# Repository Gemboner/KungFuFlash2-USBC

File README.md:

# Kung Fu Flash 2 USB-C

Cartridge for the Commodore 64 that packs a punch.

This repository is a fork of [KungFuFlash2-USBC](https://github.com/Sgw32/KungFuFlash2-USBC) which is a fork of an earlier version of [KungFuFlash2](https://codeberg.org/KimJorgensen/KungFuFlash2) from Kim Jørgensen that was later moved to Codeberg and is still being updated.

To have the "best of both worlds" (USB-C and updated firmware) this repository merged both of them together and additionally introduces some small fixes to the PCB and the production files.

Kung Fu Flash 2 is the big brother of [Kung Fu Flash](https://codeberg.org/KimJorgensen/KungFuFlash). It has a faster microcontroller with more memory and I/O pins, allowing for additional functionality.

**Currently, this project is considered experimental** and provides the same features as Kung Fu Flash, with these notable exceptions:

* CRT files are loaded into RAM, not flash, making large CRT files startup faster. However, changes to EasyFlash cartridges are lost if power is turned off, unless saved via the menu first
* The cartridge detects if the C64/C128 is reset. This allows the use of an additional reset button on the C64 or the built-in reset button on the C128
* REU emulation has been added

Kung Fu Flash 2 can emulate different cartridge types, load PRG files and use D64 disk images.
Just place your desired CRT, PRG or D64 files on a FAT formatted microSD card and use the built-in launcher to execute them.

## Hardware (Rev. 2)

There are three buttons on the cartridge; a reset button, a menu button for starting the launcher, and a special button that is used by the freezer cartridges.

A very nice case has been designed by [Bigby](https://www.printables.com/@Bigby) and can be found on [Printables](https://www.printables.com/model/119330-kung-fu-flash-cartridge-case).

Changes in hardware revision 2 are a USB-C port (including resistors) instead of micro-USB and a different crystal.

As all credits still go to Kim Jørgensen for this great cartridge, the PCB still shows his Codeberg URL.

The gerber files and BOM can be found [here](./hardware/gerber/).

## Supported Cartridges

The following cartridge types are currently supported:

* Generic cartridge (8k, 16k, Ultimax)
* Action Replay v4.x/v5/v6
* KCS Power Cartridge
* Final Cartridge III(+)
* Simons' BASIC
* Fun Play, Power Play
* Super Games
* Ocean type 1
* Epyx Fastload
* C64 Game System, System 3
* WarpSpeed
* Dinamic
* Zaxxon, Super Zaxxon
* Magic Desk, Domark, HES Australia
* Super Snapshot v5
* Comal-80
* Ross
* EasyFlash
* Prophet64
* Freeze Frame
* Freeze Machine
* MACH 5
* Pagefox
* RGCD, Hucky
* Drean
* C128 Generic cartridge (external function ROM)
* WarpSpeed 128

## Supported File Types

The following file types are currently supported:

* Cartridge (CRT)
* C64/C128 generic cartridge (ROM, BIN)
* Disk image (D64, D71, D81)
* Tape image (T64)
* Program (PRG, P00)
* SID tune (SID)
* Firmware update (UPD)
* Text document (TXT, NFO, 1ST)

## SID Playback

SID tunes can be played directly from the launcher. This feature is inherited from the
[KungFuFlash2-USBC](https://github.com/Sgw32/KungFuFlash2-USBC) fork and is not part of the original Kung Fu Flash 2.

Selecting a SID file in the file options menu offers two actions:

* "Play" (RETURN) converts the tune and starts it immediately
* "Convert to PRG" (SHIFT+RETURN) writes a PRG file next to the SID file and returns to the launcher

In both cases the tune is converted to a PRG containing a small BASIC starter and a raster interrupt player,
so the resulting file can also be used on any other C64 setup. As the PRG is written to the microSD card,
the card must not be write protected.

PSID and RSID files of version 1 to 3 are supported, with these limitations:

* Only the first subtune is played; the tune and subtune information from the SID header is ignored
* The player uses a single speed raster interrupt, so multi speed tunes will play at the wrong tempo
* Tunes that load below $0843 cannot be converted, as this area is occupied by the BASIC starter and the player

## REU Emulation

Kung Fu Flash 2 can emulate a 1 Mb REU (RAM Expansion Unit) simultaneously with disk drive emulation.
The REU is enabled in the settings menu (F5) and active when:

* A program is executed using the default option (RETURN)
* A disk image or directory is mounted using "Mount" in the file options menu (SHIFT+RETURN)
* BASIC is started via F6 (C128) or F7 (C64) in the launcher

The REU will not be active when emulating cartridges (CRT files)

## USB Port

The USB port allows programs or disk images to be transferred from/to a PC using the EasyFlash 3 USB protocol.
The USB port is active when:

* The Kung Fu Flash 2 launcher is running
* A program is started using "Load" in the file options menu (SHIFT+RETURN)
* BASIC is started via F7 in the launcher **and** REU emulation is disabled in the settings menu (F5)

Kung Fu Flash 2 shows up as a standard serial port when connected to a PC not requiring any custom drivers to be installed.
This means, however, that the EasyFlash 3 program on the PC side must be modified to support Kung Fu Flash.

The repository of the original Kung Fu Flash contains a modified version of [EasyFlash 3 USB Utilities](https://codeberg.org/KimJorgensen/KungFuFlash/src/branch/master/3rd_party/ef3utils)
and [EasyFlash 3 BBS](https://codeberg.org/KimJorgensen/KungFuFlash/src/branch/master/3rd_party/ef3bbs) which will also work with the Kung Fu Flash 2.

## Firmware Update

Just place the KungFuFlash2_v2.xx.upd file on the SD card and select the file in the launcher to initiate the firmware update.
The newest firmware can be found [here](https://github.com/JuergenLeber/KungFuFlash2-USBC/releases).

For initial firmware installation, [see here](firmware/README.md).

## Limitations

Kung Fu Flash 2 is a so called Software Defined Cartridge where a fast microcontroller emulates cartridge hardware in software.
This makes it extremely flexible, allowing different cartridge types to be supported at a relative low cost.

However, it can be challenging to get the C64 bus timing correct in software and in some places the timing is very close to the limit.
Even though Kung Fu Flash 2 has been tested on different models of the Commodore 64, there is a chance that it doesn't work correctly on your specific model, or requires [phi2 offset adjustment](firmware/README.md#diagnostic).
Use it at your own risk!

Kung Fu Flash 2 will work with the PAL and NTSC version of the Commodore 64 or Commodore 128.

Disk drive emulation is using kernal vectors and will not work with fast loaders or software that uses direct hardware access which a lot of games does.
Currently REL files are not supported and only a subset of the Commodore DOS commands are supported.

## Thanks

Kung Fu Flash 2 was based on or uses other open source projects:

* [Kung Fu Flash](https://codeberg.org/KimJorgensen/KungFuFlash)
* [EasyFlash 3](https://bitbucket.org/skoe/easyflash) by Thomas Giesel
* [Draco Browser](https://csdb.dk/release/?id=89910) by Sascha Bader
* [fatfs-stm32](https://github.com/colosimo/fatfs-stm32) by Aurelio Colosimo
* [FatFs](http://elm-chan.org/fsw/ff/00index_e.html) by ChaN
* [libusb_stm32](https://github.com/dmitrystu/libusb_stm32) by Dmitry Filimonchuk
* [OpenC64Cart](https://github.com/SukkoPera/OpenC64Cart) by Giorgioggì
* [Disk2easyflash](https://csdb.dk/release/?id=150323) by ALeX Kazik

and a few others. Please check the individual files for their license.

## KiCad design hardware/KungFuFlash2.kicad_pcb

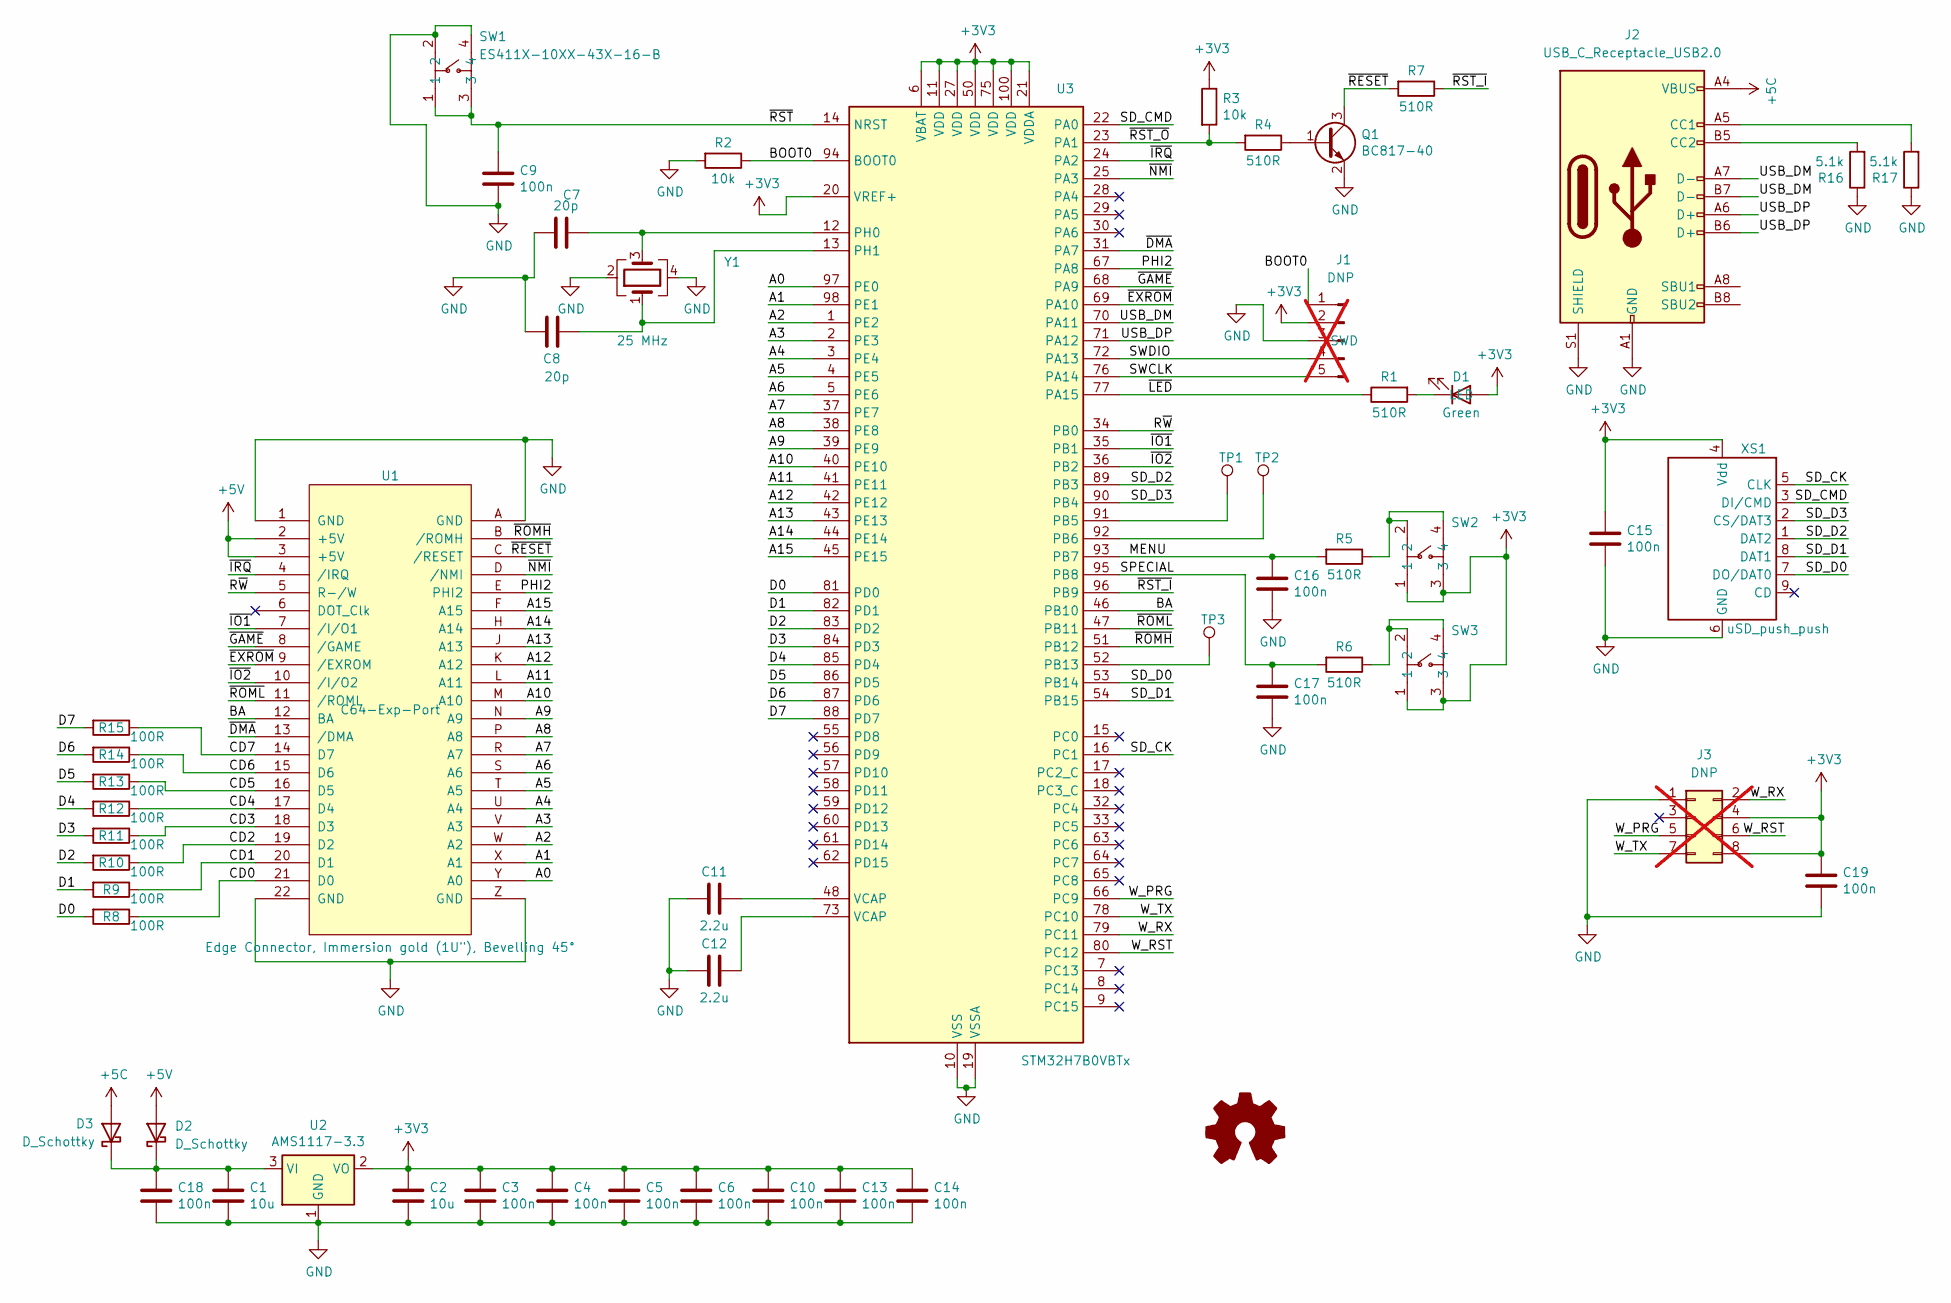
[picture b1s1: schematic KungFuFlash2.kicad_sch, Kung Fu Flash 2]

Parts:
C1, C2: 10u; C_0805_2012Metric_Pad1.18x1.45mm_HandSolder; LCSC Part# C318691
C3, C4, C5, C6, C9, C10, C13, C14, C15, C16, C17, C18, C19: 100n; C_0402_1005Metric; LCSC Part# C1591
C7, C8: 20p; C_0402_1005Metric; LCSC Part# C346210
C11, C12: 2.2u; C_0805_2012Metric_Pad1.18x1.45mm_HandSolder; LCSC Part# C5362585
D1: Green; LED_0805_2012Metric; LCSC Part# C2297
D2, D3: D_Schottky; D_SMA; LCSC Part# C64998
J1: DNP; PinHeader_1x05_P2.54mm_Vertical; LCSC Part# DNP; not fitted
J2: USB_C_Receptacle_USB2.0; USB_C_Receptacle_XKB_U262-16XN-4BVC11; LCSC Part# C165948
J3: DNP; PinSocket_2x04_P2.54mm_Vertical; LCSC Part# DNP; not fitted
Q1: BC817-40; SOT-23; LCSC Part# C916383
R1, R4, R5, R6, R7: 510R; R_0402_1005Metric; LCSC Part# C139861
R2, R3: 10k; R_0402_1005Metric; LCSC Part# C115309
R8, R9, R10, R11, R12, R13, R14, R15: 100R; R_0402_1005Metric; LCSC Part# C115424
R16, R17: 5.1k; R_0402_1005Metric; LCSC Part# C118848
SW1, SW2, SW3: ES411X-10XX-43X-16-B; SW-SMD_4P-L4.5-W4.5-P3.00-LS6.7; LCSC Part C55271185
TP1, TP2, TP3: TestPoint_Pad_1.0x1.0mm; LCSC Part# DNP
U1: Edge Connector, Immersion gold (1U"), Bevelling 4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; C64-Cart; LCSC Part# DNP
U2: AMS1117-3.3; SOT-223-3_TabPin2; LCSC Part# C6186
U3: STM32H7B0VBTx; LQFP-100_14x14mm_P0.5mm; LCSC Part# C730227
XS1: uSD_push_push; Conn_uSDcard; LCSC Part# C111196
Y1: 25 MHz; Crystal_SMD_3225-4Pin_3.2x2.5mm; LCSC Part# C9006

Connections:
+3V3: C2.1, C3.1, C4.1, C5.1, C6.1, C10.1, C13.1, C14.1, C15.1, C19.1, D1.2 (A), J1.2, J3.4, J3.8, R3.1, SW2.1, SW2.3, SW3.1, SW3.3, U2.2 (VO), U3.6 (VBAT), U3.11 (VDD), U3.20 (VREF+), U3.21 (VDDA), U3.27 (VDD), U3.50 (VDD), U3.75 (VDD), U3.100 (VDD), XS1.4 (Vdd)
+5C: D3.2 (A), J2.A4 (VBUS), J2.A9 (VBUS), J2.B4 (VBUS), J2.B9 (VBUS)
+5V: D2.2 (A), U1.2 (+5V), U1.3 (+5V)
/A0: U1.Y (A0), U3.97 (PE0)
/A1: U1.X (A1), U3.98 (PE1)
/A2: U1.W (A2), U3.1 (PE2)
/A3: U1.V (A3), U3.2 (PE3)
/A4: U1.U (A4), U3.3 (PE4)
/A5: U1.T (A5), U3.4 (PE5)
/A6: U1.S (A6), U3.5 (PE6)
/A7: U1.R (A7), U3.37 (PE7)
/A8: U1.P (A8), U3.38 (PE8)
/A9: U1.N (A9), U3.39 (PE9)
/A10: U1.M (A10), U3.40 (PE10)
/A11: U1.L (A11), U3.41 (PE11)
/A12: U1.K (A12), U3.42 (PE12)
/A13: U1.J (A13), U3.43 (PE13)
/A14: U1.H (A14), U3.44 (PE14)
/A15: U1.F (A15), U3.45 (PE15)
/BA: U1.12 (BA), U3.46 (PB10)
/BOOT0: J1.1, R2.1, U3.94 (BOOT0)
/CD0: R8.1, U1.21 (D0)
/CD1: R9.1, U1.20 (D1)
/CD2: R10.1, U1.19 (D2)
/CD3: R11.1, U1.18 (D3)
/CD4: R12.1, U1.17 (D4)
/CD5: R13.1, U1.16 (D5)
/CD6: R14.1, U1.15 (D6)
/CD7: R15.1, U1.14 (D7)
/D0: R8.2, U3.81 (PD0)
/D1: R9.2, U3.82 (PD1)
/D2: R10.2, U3.83 (PD2)
/D3: R11.2, U3.84 (PD3)
/D4: R12.2, U3.85 (PD4)
/D5: R13.2, U3.86 (PD5)
/D6: R14.2, U3.87 (PD6)
/D7: R15.2, U3.88 (PD7)
/MENU: C16.1, R5.2, U3.93 (PB7)
/PHI2: U1.E (PHI2), U3.67 (PA8)
/R~W: U1.5 (R-/W), U3.34 (PB0)
/SD_CK: U3.16 (PC1), XS1.5 (CLK)
/SD_CMD: U3.22 (PA0), XS1.3 (DI/CMD)
/SD_D0: U3.53 (PB14), XS1.7 (DO/DAT0)
/SD_D1: U3.54 (PB15), XS1.8 (DAT1)
/SD_D2: U3.89 (PB3), XS1.1 (DAT2)
/SD_D3: U3.90 (PB4), XS1.2 (CS/DAT3)
/SPECIAL: C17.1, R6.2, U3.95 (PB8)
/SWCLK: J1.5, U3.76 (PA14)
/SWDIO: J1.4, U3.72 (PA13)
/USB_DM: J2.A7 (D-), J2.B7 (D-), U3.70 (PA11)
/USB_DP: J2.A6 (D+), J2.B6 (D+), U3.71 (PA12)
/W_PRG: J3.5, U3.66 (PC9)
/W_RST: J3.6, U3.80 (PC12)
/W_RX: J3.2, U3.79 (PC11)
/W_TX: J3.7, U3.78 (PC10)
/~DMA: U1.13 (/DMA), U3.31 (PA7)
/~EXROM: U1.9 (/EXROM), U3.69 (PA10)
/~GAME: U1.8 (/GAME), U3.68 (PA9)
/~IO1: U1.7 (/I/O1), U3.35 (PB1)
/~IO2: U1.10 (/I/O2), U3.36 (PB2)
/~IRQ: U1.4 (/IRQ), U3.24 (PA2)
/~LED: R1.1, U3.77 (PA15)
/~NMI: U1.D (/NMI), U3.25 (PA3)
/~RESET: Q1.3 (C), R7.2, U1.C (/RESET)
/~ROMH: U1.B (/ROMH), U3.51 (PB12)
/~ROML: U1.11 (/ROML), U3.47 (PB11)
/~RST_I: R7.1, U3.96 (PB9)
/~RST_O: R3.2, R4.2, U3.23 (PA1)
/~RST: C9.1, SW1.1, SW1.3, U3.14 (NRST)
GND: C1.2, C2.2, C3.2, C4.2, C5.2, C6.2, C7.1, C8.1, C9.2, C10.2, C11.1, C12.2, C13.2, C14.2, C15.2, C16.2, C17.2, C18.2, C19.2, J1.3, J2.A1 (GND), J2.A12 (GND), J2.B1 (GND), J2.B12 (GND), J2.S1 (SHIELD), J3.1, Q1.2 (E), R2.2, R16.1, R17.1, SW1.2, SW1.4, U1.1 (GND), U1.22 (GND), U1.A (GND), U1.Z (GND), U2.1 (GND), U3.10 (VSS), U3.19 (VSSA), U3.26 (VSS), U3.49 (VSS), U3.74 (VSS), U3.99 (VSS), XS1.6 (GND), Y1.2, Y1.4
unnamed: C11.2, U3.48 (VCAP)
unnamed: C12.1, U3.73 (VCAP)
unnamed: D1.1 (K), R1.2
unnamed: C1.1, C18.1, D2.1 (K), D3.1 (K), U2.3 (VI)
unnamed: J2.A5 (CC1), R17.2
unnamed: J2.B5 (CC2), R16.2
unnamed: Q1.1 (B), R4.1
unnamed: R5.1, SW2.2, SW2.4
unnamed: R6.1, SW3.2, SW3.4
unnamed: TP1.1 (1_1), U3.91 (PB5)
unnamed: TP2.1 (1_1), U3.92 (PB6)
unnamed: TP3.1 (1_1), U3.52 (PB13)
unnamed: C7.2, U3.12 (PH0), Y1.3
unnamed: C8.2, U3.13 (PH1), Y1.1

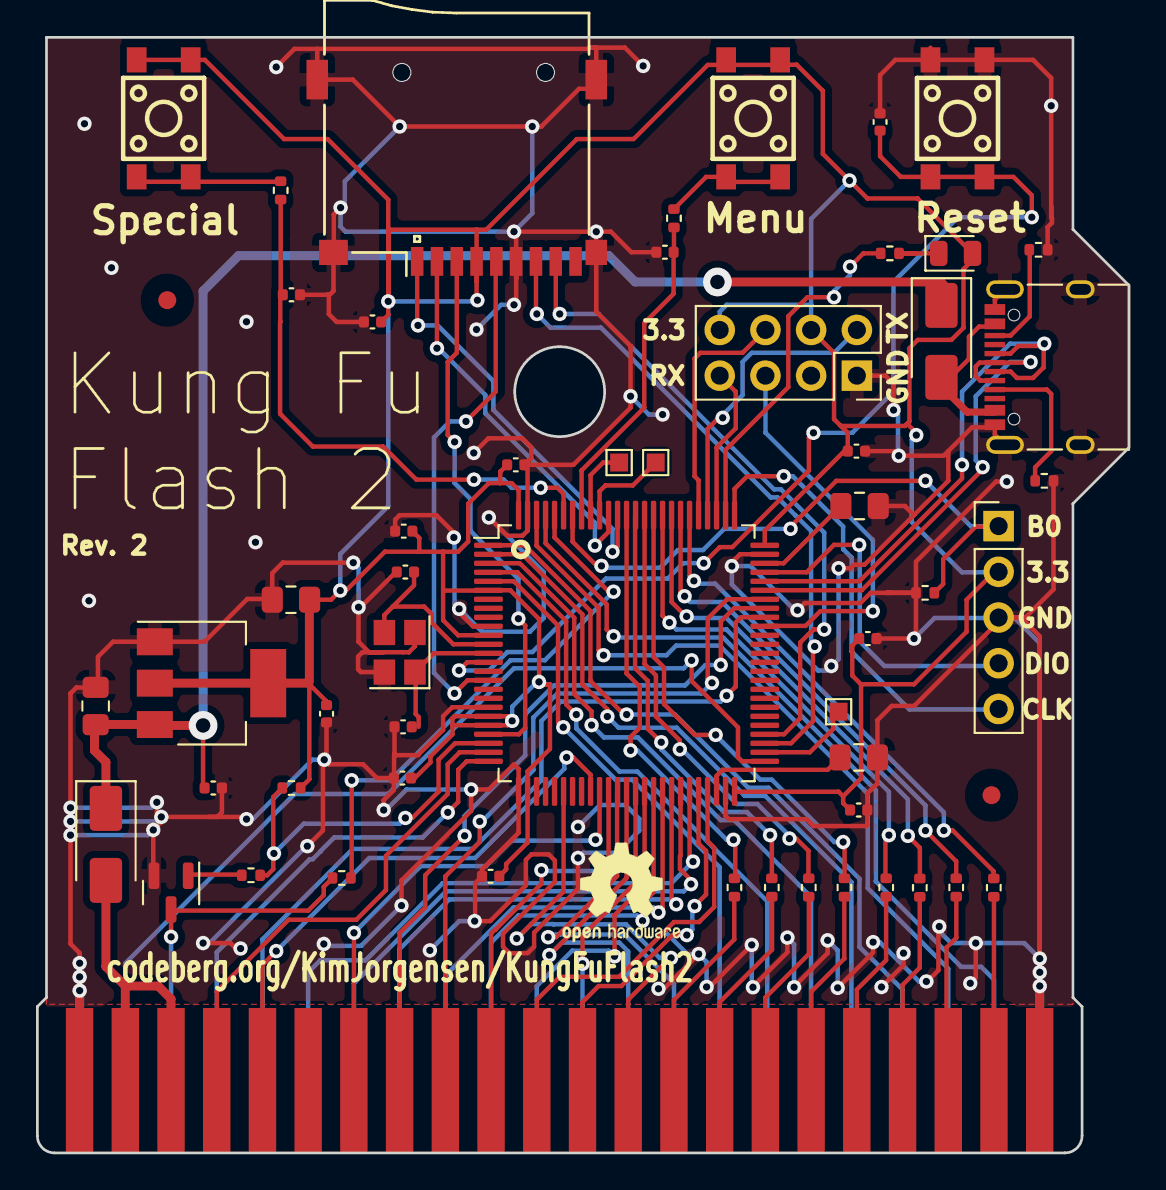
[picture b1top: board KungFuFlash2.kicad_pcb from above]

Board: 2 copper layers, 60.6 x 62.0 mm, 54 parts (0 on the bottom side), 84 nets.

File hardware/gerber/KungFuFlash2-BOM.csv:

"#","Reference","Qty","Manf","Manf#","LCSC Part#","Description","Value","Footprint","DNP"
"1","C1,C2","2","Samsung Electro-Mechanics","CL21A106KAYNNNG","C318691","","10u","Capacitor_SMD:C_0805_2012Metric_Pad1.18x1.45mm_HandSolder",""
"2","C3,C4,C5,C6,C9,C10,C13,C14,C15,C16,C17,C18,C19","13","Samsung Electro-Mechanics","CL10B104KB8NNNC","C1591","","100n","Capacitor_SMD:C_0603_1608Metric_Pad1.08x0.95mm_HandSolder",""
"3","C7,C8","2","Samsung Electro-Mechanics","CL10C200JB81PNC","C346210","","20p","Capacitor_SMD:C_0603_1608Metric_Pad1.08x0.95mm_HandSolder",""
"4","C11,C12","2","Samsung Electro-Mechanics","CL21B225KBYVPNE","C5362585","","2.2u","Capacitor_SMD:C_0805_2012Metric_Pad1.18x1.45mm_HandSolder",""
"5","D1","1","Hubei KENTO Elec","KT-0805G","C2297","LED","Green","LED_SMD:LED_0805_2012Metric_Pad1.15x1.40mm_HandSolder",""
"6","D2,D3","2","MDD","SS33","C64998","","D_Schottky","Diode_SMD:D_SMA_Handsoldering",""
"7","J1","1","DNP","DNP","DNP","SWD","DNP","Connector_PinHeader_2.54mm:PinHeader_1x05_P2.54mm_Vertical","DNP"
"8","J2","1","Korean Hroparts Elec","TYPE-C-31-M-12","C165948","USB-C","USB_C_Receptacle_USB2.0","Connector_USB:USB_C_Receptacle_XKB_U262-16XN-4BVC11",""
"9","J3","1","DNP","DNP","DNP","WiFi-Module","DNP","Connector_PinSocket_2.54mm:PinSocket_2x04_P2.54mm_Vertical","DNP"
"10","Q1","1","JSMSEMI","BC817","C916383","","BC817-40","Package_TO_SOT_SMD:SOT-23",""
"11","R1,R4,R5,R6,R7","5","FH","RS-05K5100FT","C139861","","510R","Resistor_SMD:R_0805_2012Metric_Pad1.20x1.40mm_HandSolder",""
"12","R2,R3","2","FH","RS-05K1002FT","C115309","","10k","Resistor_SMD:R_0805_2012Metric_Pad1.20x1.40mm_HandSolder",""
"13","R8,R9,R10,R11,R12,R13,R14,R15","8","FH","RS-05K1000FT","C115424","","100R","Resistor_SMD:R_0805_2012Metric_Pad1.20x1.40mm_HandSolder",""
"14","R16,R17","2","FH","RS-05K5101FT","C118848","","5.1k","Resistor_SMD:R_0805_2012Metric_Pad1.20x1.40mm_HandSolder",""
"15","SW1,SW2,SW3","3","SHOU HAN","SH-6X6X5H-CJ","C42416245","Reset, Menu, Special","Tactile Switch SPST 250gf 5mm PC Pin 6mm x 6mm Through Hole","Button_Switch_THT:SW_PUSH_6mm_H8mm",""
"16","U2","1","Advanced Monolithic Systems","AMS1117-3.3","C6186","","AMS1117-3.3","Package_TO_SOT_SMD:SOT-223-3_TabPin2",""
"17","U3","1","ST","STM32H7B0VBT6","C730227","","STM32H7B0VBTx","Package_QFP:LQFP-100_14x14mm_P0.5mm",""
"18","XS1","1","SOFNG","TF-15x15","C111196","","uSD_push_push","KungFuFlash2:Conn_uSDcard",""
"19","Y1","1","YXC Crystal Oscillators","X322525MOB4SI","C9006","","25 MHz","Crystal:Crystal_SMD_3225-4Pin_3.2x2.5mm",""

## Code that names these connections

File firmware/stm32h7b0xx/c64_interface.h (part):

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 */

/******************************************************************************
* C64 address bus on PE0-PE15
* Returned as 32 bit value for performance
******************************************************************************/
#define C64_ADDR_READ() (GPIOE->IDR)

#define C64_ADDR_WRITE(addr)                    \
    /* Make PE0-PE15 outout */                  \
    GPIOE->MODER = 0x55555555;                  \
    GPIOE->ODR = addr

#define C64_ADDR_INPUT()                        \
    /* Make PE0-PE15 input */                   \
    GPIOE->MODER = 0

/******************************************************************************
* C64 data bus on PD0-PD7
* Returned as 32 bit value for performance
******************************************************************************/
#define C64_DATA_READ() (GPIOD->IDR)

#define C64_DATA_WRITE(data)                    \
    /* Make PD0-PD7 outout */                   \
    *((volatile u16 *)&GPIOD->MODER) = 0x5555;  \
    *((volatile u8 *)&GPIOD->ODR) = (data);     \
    COMPILER_BARRIER()

#define C64_DATA_INPUT()                        \
    /* Make PD0-PD7 input */                    \
    *((volatile u16 *)&GPIOD->MODER) = 0x0000;  \
    COMPILER_BARRIER()

/******************************************************************************
* C64 control bus on PB0-PB2 and PB10-PB12, and C64 reset detect on PB9
* Menu button & special button on PB7 & PB8
* Returned as 32 bit value for performance
******************************************************************************/
#define C64_WRITE_HIGH  GPIO_BSRR_BS0
#define C64_WRITE_LOW   GPIO_BSRR_BR0

#define C64_WRITE       GPIO_IDR_ID0    // R/W on PB0
#define C64_IO1         GPIO_IDR_ID1    // IO1 on PB1
#define C64_IO2         GPIO_IDR_ID2    // IO1 on PB2

#define MENU_BTN        GPIO_IDR_ID7    // Menu button on PB7
#define SPECIAL_BTN     GPIO_IDR_ID8    // Special button on PB8
#define C64_RESET       GPIO_IDR_ID9    // Reset detect on PB9

#define C64_BA          GPIO_IDR_ID10   // BA on PB10
#define C64_ROML        GPIO_IDR_ID11   // ROML on PB11
#define C64_ROMH        GPIO_IDR_ID12   // ROMH on PB12

#define C64_CONTROL_READ()          (GPIOB->IDR)
#define C64_CONTROL_WRITE(state)    GPIOB->BSRR = (state)

static void c64_reset_detect_enable(void)
{
    // Enable PB9 interrupt
    EXTI->PR1 = EXTI_PR1_PR9;
    EXTI->IMR1 |= EXTI_IMR1_IM9;
}

static inline void c64_reset_detect_disable(void)
{
    // Disable PB9 interrupt
    EXTI->IMR1 &= ~EXTI_IMR1_IM9;
}

/******************************************************************************
* C64 IRQ and NMI on PA2 & PA3
* C64 DMA, GAME, and EXROM on PA7 & PA9-PA10
* Status LED on PA15
******************************************************************************/
#define C64_IRQ_HIGH        GPIO_BSRR_BS2
#define C64_IRQ_LOW         GPIO_BSRR_BR2
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}

/******************************************************************************
* C64 clock input on PA8 (timer 1)
******************************************************************************/

// C64_BUS_HANDLER timing
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    (void)TIM1->SR

/******************************************************************************
* C64 reset on PA1
******************************************************************************/

static void c64_reset_release(void);
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

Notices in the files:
firmware/stm32h7b0xx/c64_interface.h:
Copyright (c) 2019-2026 Kim Jørgensen
